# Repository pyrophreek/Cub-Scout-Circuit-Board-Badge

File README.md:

# Cub-Scout-Circuit-Board-Badge
A wolf-shaped badge with blinking eyes for Cub Scouts to learn the basics of circuit board assembly and some basic circuit components.

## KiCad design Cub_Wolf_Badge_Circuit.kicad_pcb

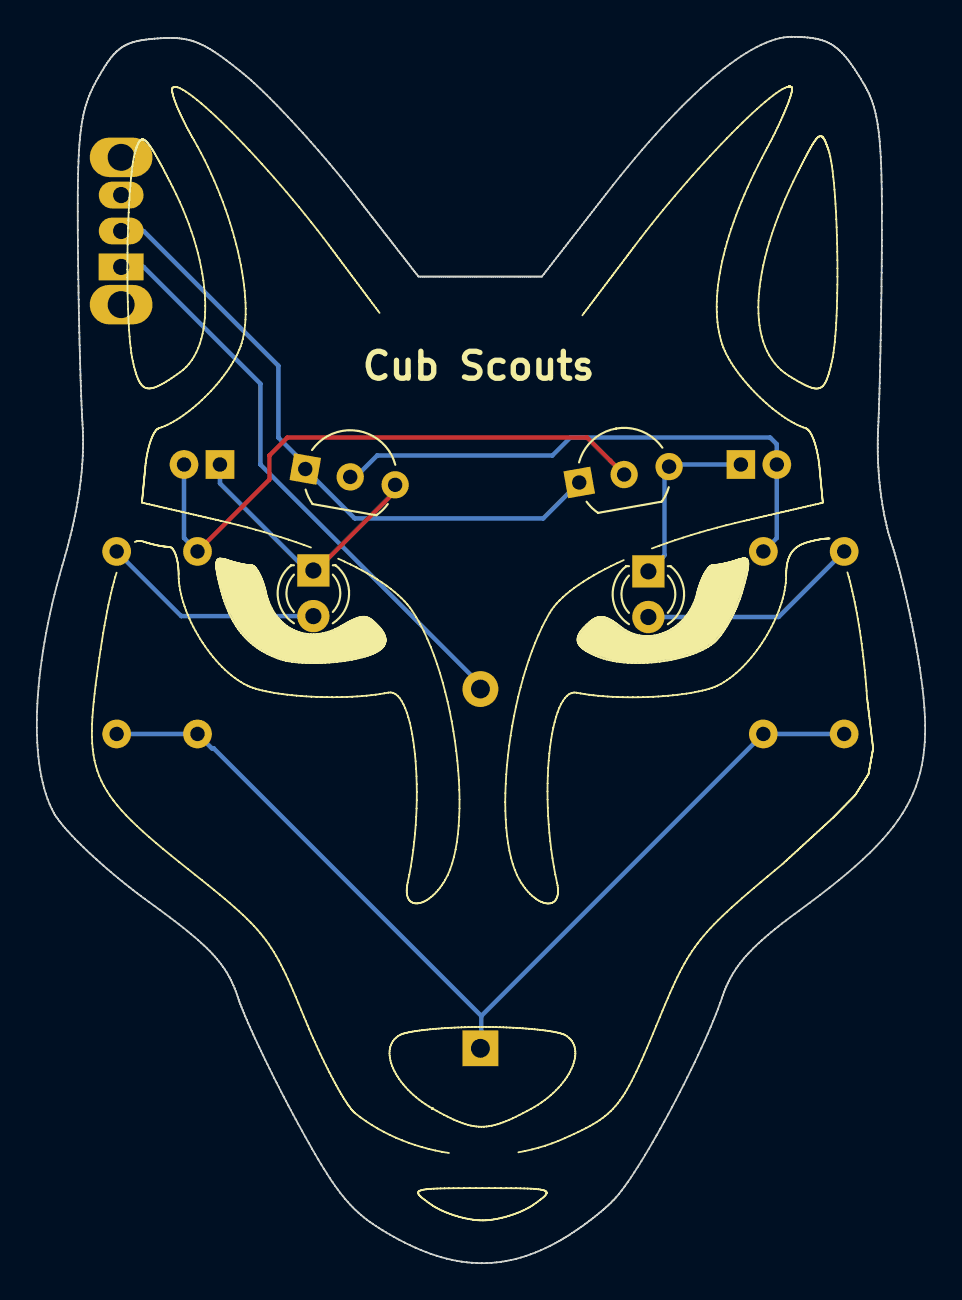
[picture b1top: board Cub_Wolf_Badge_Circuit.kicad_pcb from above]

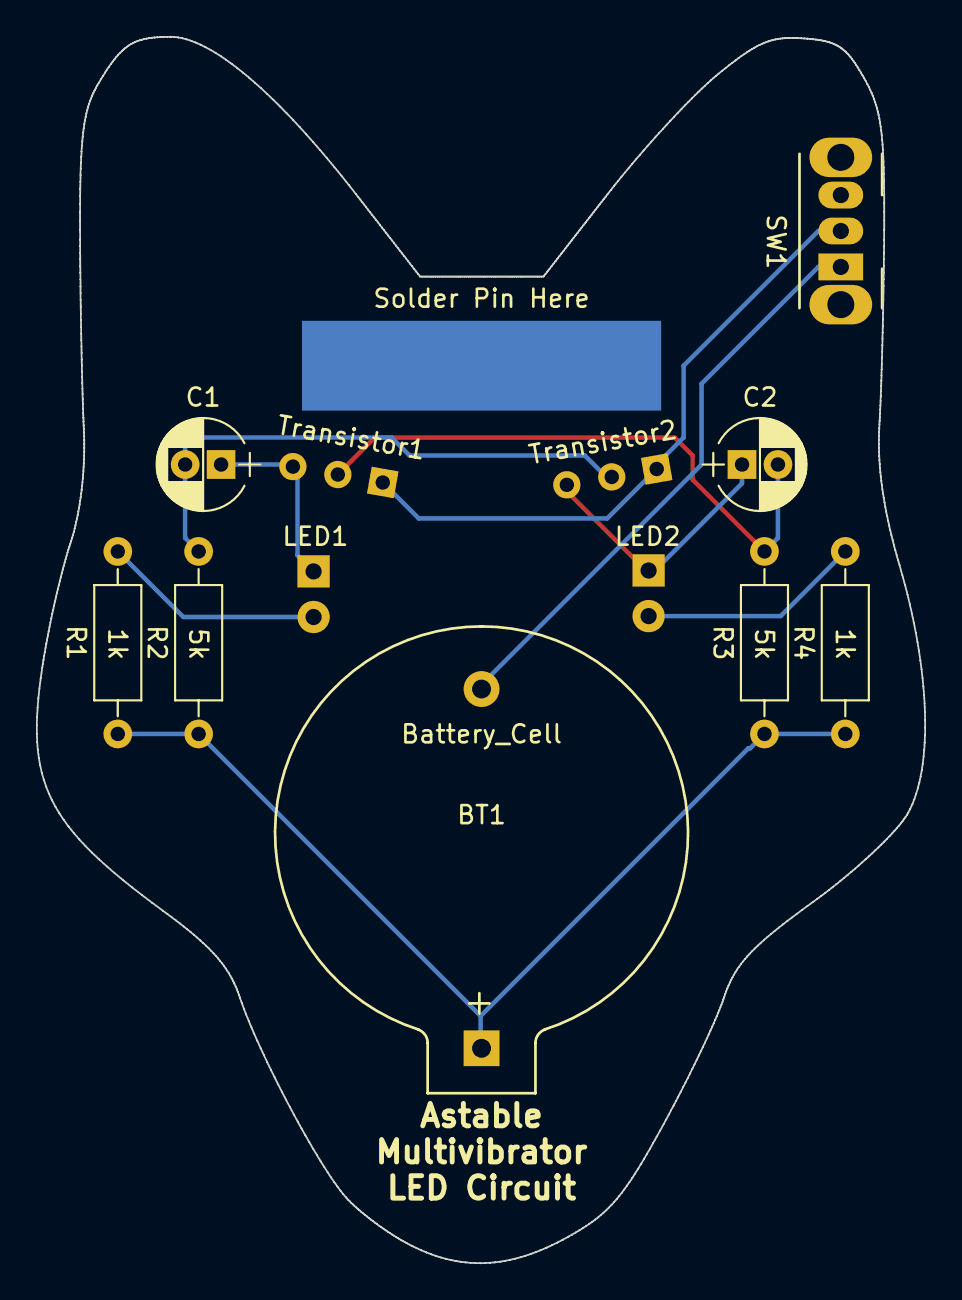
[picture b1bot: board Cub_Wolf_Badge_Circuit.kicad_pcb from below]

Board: 2 copper layers, 49.5 x 68.3 mm, 13 parts (9 on the bottom side), 9 nets.

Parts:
BT1: Battery_Cell; 1x20mm-CoinCell
C1, C2: 220uF; CP_Radial_D5.0mm_P2.00mm
LED1, LED2: LED; LED_D3.0mm
R1, R4: 1k; R_Axial_DIN0207_L6.3mm_D2.5mm_P10.16mm_Horizontal
R2, R3: 5k; R_Axial_DIN0207_L6.3mm_D2.5mm_P10.16mm_Horizontal
SW1: SW_SPDT; SW_CuK_OS102011MA1QN1_SPDT_Angled
Solder Pin Here: SolderWirePad_single_SMD_5x10mm
Transistor1, Transistor2: 2N3904; TO-92_Inline_Wide

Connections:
unnamed: BT1.1, R1.1, R2.1, R3.1, R4.1
unnamed: BT1.2, SW1.1
unnamed: C1.1, LED1.1, Transistor1.3
unnamed: C1.2, R2.2, Transistor2.2
unnamed: C2.1, LED2.1, Transistor2.3
unnamed: C2.2, R3.2, Transistor1.2
unnamed: LED1.2, R1.2
unnamed: LED2.2, R4.2
unnamed: SW1.2, Transistor1.1, Transistor2.1

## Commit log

2019-03-04 Initial Upload of Files
2019-03-04 Updated trace placement on switch, updated resistor values.
2019-03-04 V2 Final Design files
    Minor changes to silkscreen and placement. Moved battery holder up to hopefully look better.
